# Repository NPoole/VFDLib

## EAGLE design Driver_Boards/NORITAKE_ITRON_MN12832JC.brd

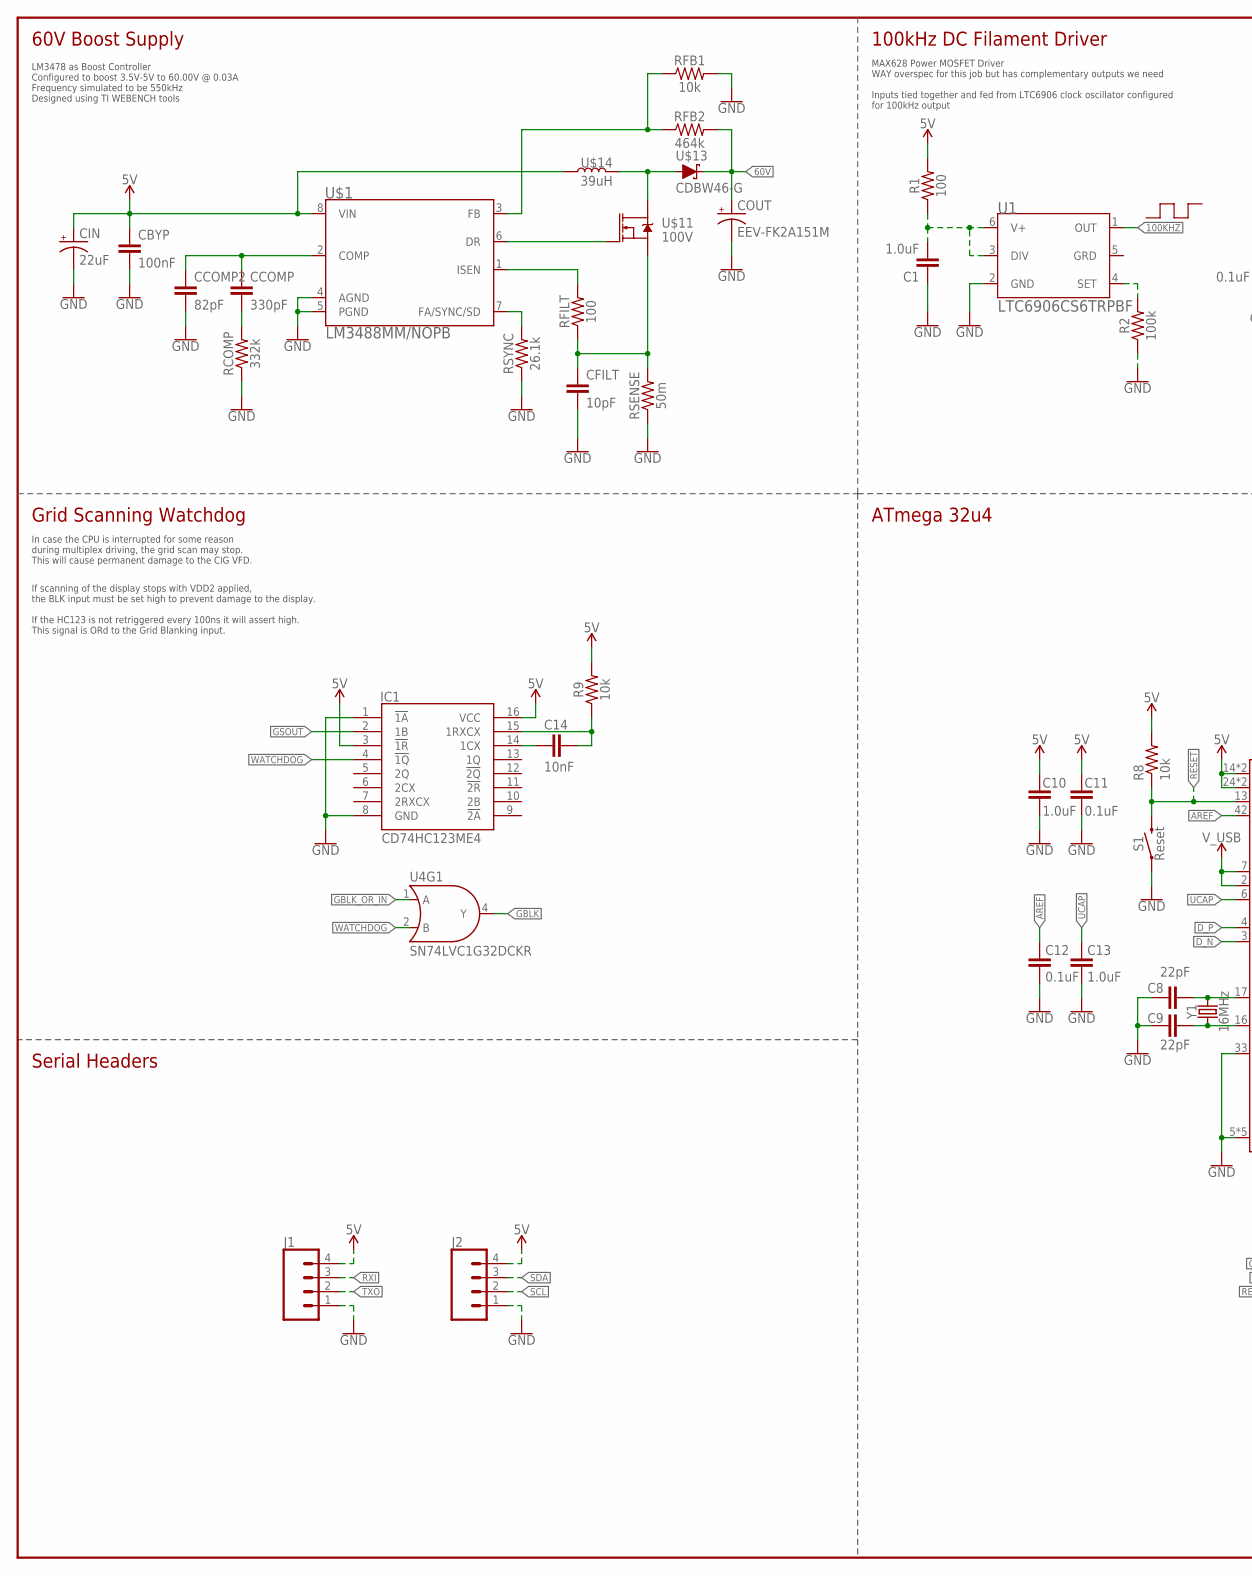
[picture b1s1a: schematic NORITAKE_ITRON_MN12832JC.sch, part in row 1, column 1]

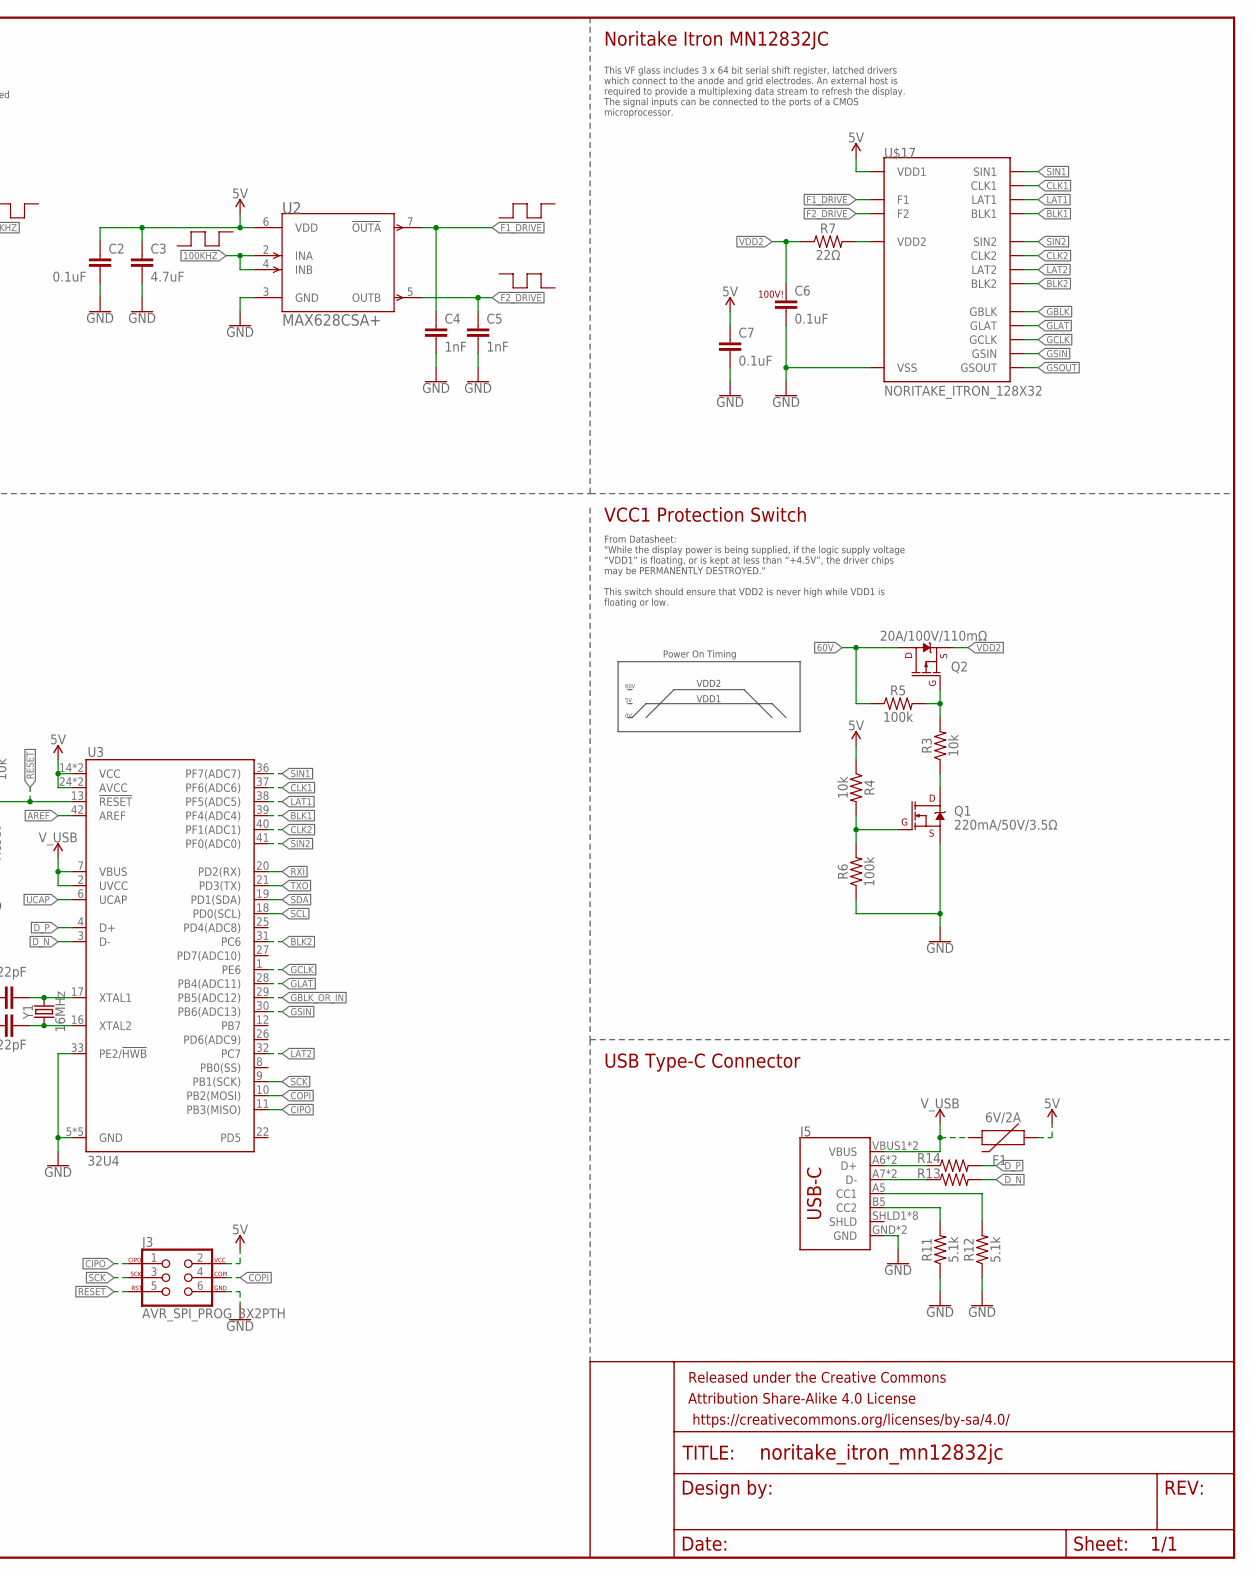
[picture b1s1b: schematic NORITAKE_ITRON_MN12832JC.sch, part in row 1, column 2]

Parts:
C1, C10, C13: 1.0uF; 0603
C2, C6, C7, C11, C12: 0.1uF; 0603
C3: 4.7uF; 0603
C4, C5: 1nF; 0603
C8, C9: 22pF; 0603
C14: 10nF; 0603
CBYP: 100nF; 0805
CCOMP: 330pF; 0805
CCOMP2: 82pF; 0805
CFILT: 10pF; 0603
CIN: 22uF; SM_RADIAL_C
COUT: EEV-FK2A151M; SM_RADIAL_J16
F1: 6V/2A; 1210
FRAME1: FRAME-LEDGERNO_FOOTPRINT; DUMMY
IC1: CD74HC123ME4; SOIC127P600X175-16N
J1, J2: CONN_04PTH; 1X04
J3: AVR_SPI_PROG_3X2PTH; 2X3
J5: USB_C5; USB-C-16P-5
Q1: 220mA/50V/3.5Ω; SOT23-3
Q2: 20A/100V/110mΩ; TO-252/DPAK
R1: 100; 0603
R2, R5, R6: 100k; 0603
R3, R4, R8, R9: 10k; 0603
R7, R13, R14: 22Ω; 0603
R11, R12: 5.1k; 0603
RCOMP: 332k; 0603
RFB1: 10k; 0603
RFB2: 464k; 0603
RFILT: 100; 0603
RSENSE: 50m; 0603
RSYNC: 26.1k; 0603
S1: Reset; TACTILE_SWITCH_SMD_4.6X2.8MM
U1: LTC6906CS6TRPBF; TSOT-23_6_ADI
U2: MAX628CSA+; 21-0041B_8_MXM
U3: 32U4; TQFP44
U4: SN74LVC1G32DCKR; SOT353
U$1: LM3488MM/NOPB; MUA08A
U$11: 100V; PG-TDSON-8
U$13: CDBW46-G; SOD-123
U$14: 39uH; IND_NPI54C
U$17: NORITAKE_ITRON_128X32
Y1: 16MHz; CRYSTAL-SMD-5X3.2-4PAD

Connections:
5V: C2.1, C3.1, C7.1, C10.2, C11.2, CBYP.1, CIN.1 (+), F1.1, IC1.3 (!1R), IC1.16 (VCC), J1.4, J2.4, J3.2, R1.2, R4.1, R8.2, R9.2, U2.6 (VDD), U3.14 (VCC), U3.24 (AVCC), U3.34 (VCC), U3.44 (AVCC), U$1.8 (VIN), U$14.1, U$17.P$13 (VDD1)
60V: COUT.1 (+), Q2.2 (D), R5.1, RFB2.2, U$13.1 (C)
100KHZ: U1.1 (OUT), U2.2 (INA), U2.4 (INB)
AREF: C12.2, U3.42 (AREF)
BLK1: U3.39 (PF4(ADC4)), U$17.P$4 (BLK1)
BLK2: U3.31 (PC6), U$17.P$23 (BLK2)
CIPO: J3.1, U3.11 (PB3(MISO))
CLK1: U3.37 (PF6(ADC6)), U$17.P$6 (CLK1)
CLK2: U3.40 (PF1(ADC1)), U$17.P$21 (CLK2)
COPI: J3.4, U3.10 (PB2(MOSI))
D-_HV: J5.A7 (D-), J5.B7 (D-), R13.1
DP_HV: J5.A6 (D+), J5.B6 (D+), R14.1
D_N: R13.2, U3.3 (D-)
D_P: R14.2, U3.4 (D+)
F1_DRIVE: C4.1, U2.7 (!OUTA), U$17.P$1 (F1), U$17.P$2 (F1), U$17.P$3 (F1)
F2_DRIVE: C5.1, U2.5 (OUTB), U$17.P$26 (F2), U$17.P$27 (F2), U$17.P$28 (F2)
GBLK: U4.4 (Y), U$17.P$14 (GBLK)
GBLK_OR_IN: U3.29 (PB5(ADC12)), U4.1 (A)
GCLK: U3.1 (PE6), U$17.P$16 (GCLK)
GLAT: U3.28 (PB4(ADC11)), U$17.P$15 (GLAT)
GND: C1.1, C2.2, C3.2, C4.2, C5.2, C6.2, C7.2, C8.2, C9.2, C10.1, C11.1, C12.1, C13.1, CBYP.2, CCOMP2.2, CFILT.2, CIN.2 (-), COUT.2 (-), IC1.1 (!1A), IC1.8 (GND), J1.1, J2.1, J3.6, J5.GND, J5.GND2 (GND), Q1.2 (S), R2.1, R6.1, R11.1, R12.1, RCOMP.1, RFB1.2, RSENSE.1, RSYNC.1, S1.1, S1.2 (1), U1.2 (GND), U2.3 (GND), U3.5 (GND), U3.15 (GND), U3.23 (GND), U3.33 (PE2/!HWB), U3.35 (GND), U3.43 (GND), U$1.4 (AGND), U$1.5 (PGND), U$17.P$11 (VSS), U$17.P$12 (VSS)
GSIN: U3.30 (PB6(ADC13)), U$17.P$17 (GSIN)
GSOUT: IC1.2 (1B), U$17.P$18 (GSOUT)
LAT1: U3.38 (PF5(ADC5)), U$17.P$5 (LAT1)
LAT2: U3.32 (PC7), U$17.P$22 (LAT2)
unnamed: RSYNC.2, U$1.7 (FA/SYNC/SD)
unnamed: CCOMP.1, CCOMP2.1, U$1.2 (COMP)
unnamed: RFILT.2, U$1.1 (ISEN)
unnamed: CCOMP.2, RCOMP.2
unnamed: CFILT.1, RFILT.1, RSENSE.2, U$11.1 (S), U$11.2 (S), U$11.3 (S)
unnamed: U$11.5 (D), U$11.6 (D), U$11.7 (D), U$11.8 (D), U$11.9 (D), U$13.2 (A), U$14.2
unnamed: RFB1.1, RFB2.1, U$1.3 (FB)
unnamed: U$1.6 (DR), U$11.4 (G)
unnamed: C1.2, R1.1, U1.3 (DIV), U1.6 (V+)
unnamed: R2.2, U1.4 (SET)
unnamed: R7.2, U$17.P$9 (VDD2), U$17.P$10 (VDD2)
unnamed: Q1.1 (G), R4.2, R6.2
unnamed: Q1.3 (D), R3.1
unnamed: Q2.1 (G), R3.2, R5.2
unnamed: C9.1, U3.16 (XTAL2), Y1.1
unnamed: C8.1, U3.17 (XTAL1), Y1.3 (2)
unnamed: C14.2, IC1.14 (1CX)
unnamed: C14.1, IC1.15 (1RXCX), R9.1
unnamed: J5.A5 (CC1), R12.2
unnamed: J5.B5 (CC2), R11.2
RESET: J3.5, R8.1, S1.3 (2), S1.4 (2), U3.13 (!RESET)
RXI: J1.3, U3.20 (PD2(RX))
SCK: J3.3, U3.9 (PB1(SCK))
SCL: J2.2, U3.18 (PD0(SCL))
SDA: J2.3, U3.19 (PD1(SDA))
SIN1: U3.36 (PF7(ADC7)), U$17.P$7 (SIN1)
SIN2: U3.41 (PF0(ADC0)), U$17.P$20 (SIN2)
TXO: J1.2, U3.21 (PD3(TX))
UCAP: C13.2, U3.6 (UCAP)
VDD2: C6.1, Q2.3 (S), R7.1
V_USB: F1.2, J5.VBUS1 (VBUS), J5.VBUS2 (VBUS), U3.2 (UVCC), U3.7 (VBUS)
WATCHDOG: IC1.4 (!1Q), U4.2 (B)

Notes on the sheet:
60V Boost Supply
100kHz DC Filament Driver
100V!
Noritake Itron MN12832JC
VCC1 Protection Switch
LM3478 as Boost Controller Configured to boost 3.5V-5V to 60.00V @ 0.03A Frequency simulated to be 550kHz Designed using TI WEBENCH tools
MAX628 Power MOSFET Driver WAY overspec for this job but has complementary outputs we need Inputs tied together and fed from LTC6906 clock oscillator configured for 100kHz output
From Datasheet: "While the display power is being supplied, if the logic supply voltage “VDD1” is floating, or is kept at less than “+4.5V”, the driver chips may be PERMANENTLY DESTROYED." This switch should ensure that VDD2 is never high while VDD1 is floating or low.
VDD1
VDD2
60V
Power On Timing
This VF glass includes 3 x 64 bit serial shift register, latched drivers which connect to the anode and grid electrodes. An external host is required to provide a multiplexing data stream to refresh the display. The signal inputs can be connected to the ports of a CMOS microprocessor.
ATmega 32u4
USB Type-C Connector
Grid Scanning Watchdog
In case the CPU is interrupted for some reason during multiplex driving, the grid scan may stop. This will cause permanent damage to the CIG VFD.
If scanning of the display stops with VDD2 applied, the BLK input must be set high to prevent damage to the display. If the HC123 is not retriggered every 100ns it will assert high. This signal is ORd to the Grid Blanking input.
Serial Headers

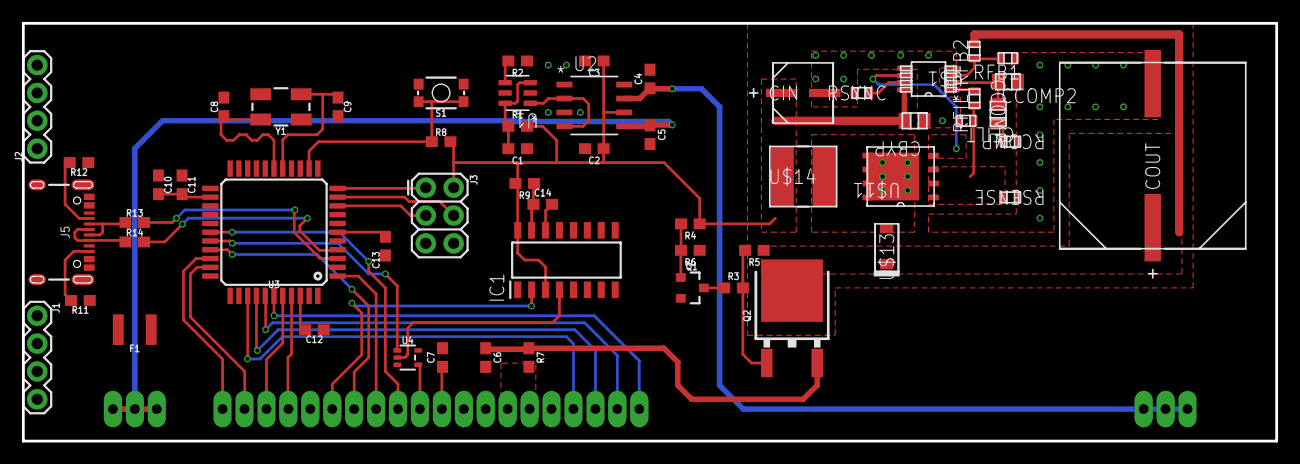
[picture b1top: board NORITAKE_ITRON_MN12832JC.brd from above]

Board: 2 copper layers, 114.3 x 38.1 mm, 59 parts (1 on the bottom side), 57 nets.

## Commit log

2021-11-15 Close to finished with Itron Driver
2021-11-16 Itron Driver ready for protos

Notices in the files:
parts and their libraries:
SparkFun-Aesthetics: Licensing: Creative Commons ShareAlike 4.0 International - https://creativecommons.org/licenses/by-sa/4.0
COPYRIGHT: Copyright (C) 2021 Ultra Librarian. All rights reserved.
SparkFun-Aesthetics: Released under the Creative Commons Attribution Share-Alike 4.0 License
